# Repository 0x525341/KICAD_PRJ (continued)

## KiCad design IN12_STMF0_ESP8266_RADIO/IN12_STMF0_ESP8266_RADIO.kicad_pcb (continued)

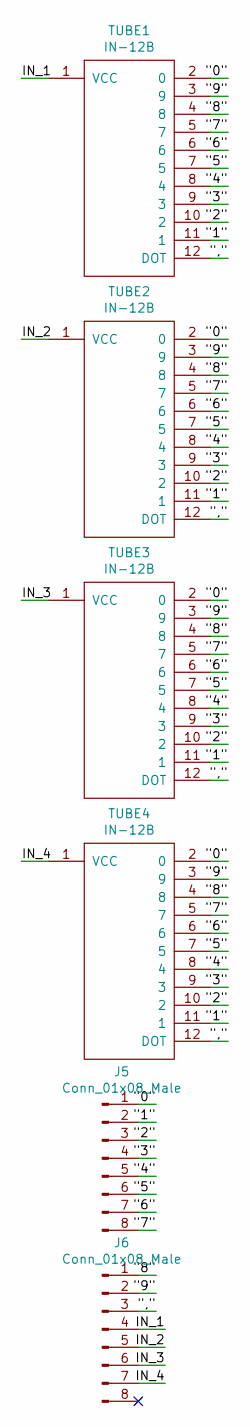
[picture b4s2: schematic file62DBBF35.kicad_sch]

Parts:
J5, J6: Conn_01x08_Male; PinHeader_1x08_P2.54mm_Vertical
TUBE1, TUBE2, TUBE3, TUBE4: IN-12B

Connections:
/Sheet62DBBF35/"0": J5.1, TUBE1.2 (0), TUBE2.2 (0), TUBE3.2 (0), TUBE4.2 (0)
/Sheet62DBBF35/"1": J5.2, TUBE1.11 (1), TUBE2.11 (1), TUBE3.11 (1), TUBE4.11 (1)
/Sheet62DBBF35/"2": J5.3, TUBE1.10 (2), TUBE2.10 (2), TUBE3.10 (2), TUBE4.10 (2)
/Sheet62DBBF35/"3": J5.4, TUBE1.9 (3), TUBE2.9 (3), TUBE3.9 (3), TUBE4.9 (3)
/Sheet62DBBF35/"4": J5.5, TUBE1.8 (4), TUBE2.8 (4), TUBE3.8 (4), TUBE4.8 (4)
/Sheet62DBBF35/"5": J5.6, TUBE1.7 (5), TUBE2.7 (5), TUBE3.7 (5), TUBE4.7 (5)
/Sheet62DBBF35/"6": J5.7, TUBE1.6, TUBE2.6, TUBE3.6, TUBE4.6
/Sheet62DBBF35/"7": J5.8, TUBE1.5 (7), TUBE2.5 (7), TUBE3.5 (7), TUBE4.5 (7)
/Sheet62DBBF35/"8": J6.1, TUBE1.4 (8), TUBE2.4 (8), TUBE3.4 (8), TUBE4.4 (8)
/Sheet62DBBF35/"9": J6.2, TUBE1.3 (9), TUBE2.3 (9), TUBE3.3 (9), TUBE4.3 (9)
/Sheet62DBBF35/",": J6.3, TUBE1.12 (DOT), TUBE2.12 (DOT), TUBE3.12 (DOT), TUBE4.12 (DOT)
/Sheet62DBBF35/IN_1: J6.4, TUBE1.1 (VCC)
/Sheet62DBBF35/IN_2: J6.5, TUBE2.1 (VCC)
/Sheet62DBBF35/IN_3: J6.6, TUBE3.1 (VCC)
/Sheet62DBBF35/IN_4: J6.7, TUBE4.1 (VCC)

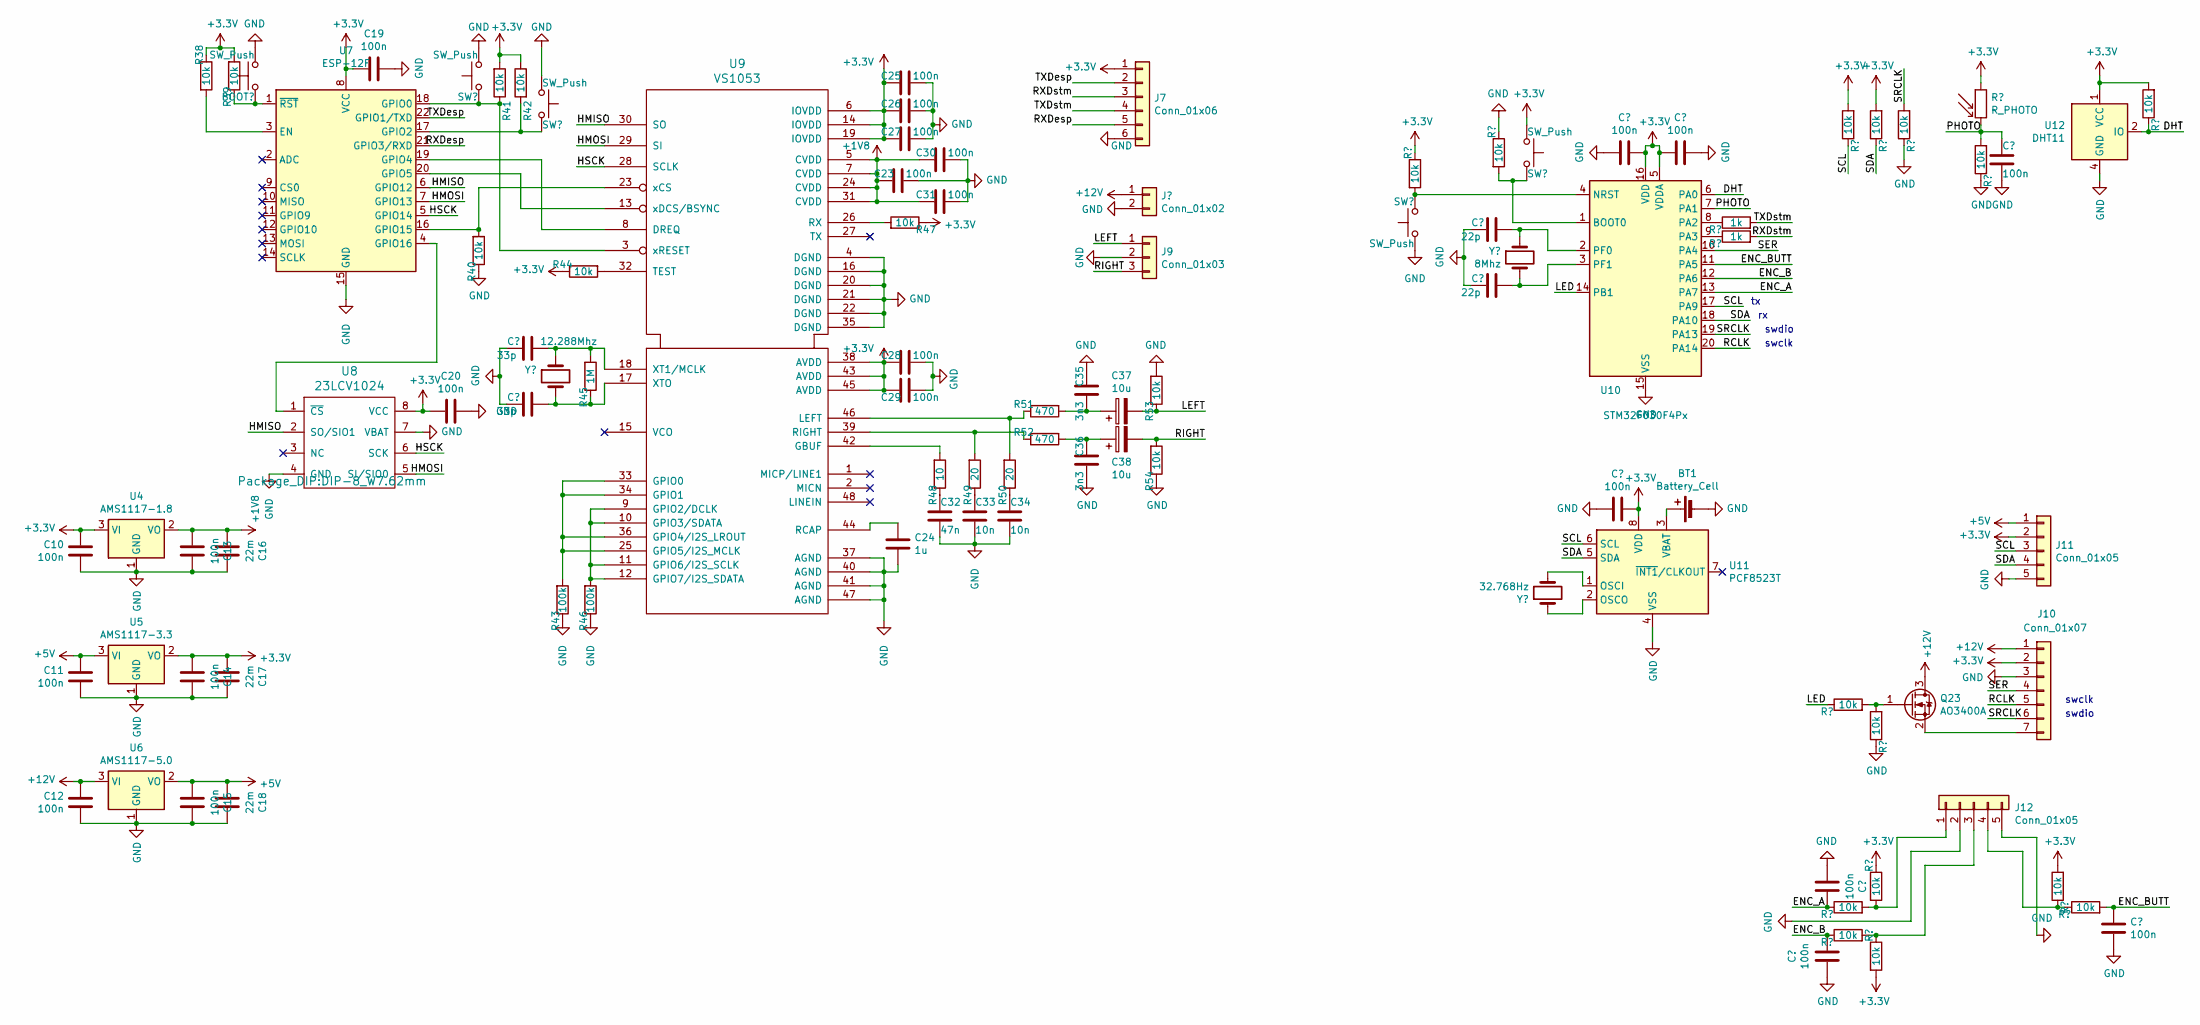
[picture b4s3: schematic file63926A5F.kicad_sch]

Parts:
BOOT1, BOOT2, BOOT3: SW_Push; SW_SPST_B3U-1000P
BT1: Battery_Cell; PinHeader_1x02_P2.54mm_Vertical
C10, C11, C12, C13, C14, C15, C19, C20, C23, C25, C26, C27, C28, C29, C30, C31, C41, C42, C43, C44, C45, C46, C47: 100n; C_1206_3216Metric
C16, C17, C18: 22m; C_1206_3216Metric
C21, C22: 33p; C_1206_3216Metric
C24: 1u; C_1206_3216Metric
C32: 47n; C_1206_3216Metric
C33, C34: 10n; C_1206_3216Metric
C35, C36: 3n3; C_1206_3216Metric
C37, C38: 10u; CP_Radial_D5.0mm_P2.00mm
C39, C40: 22p; C_1206_3216Metric
J7: Conn_01x06; PinHeader_1x06_P2.54mm_Vertical
J8: Conn_01x02; TerminalBlock_Phoenix_PT-1,5-2-5.0-H_1x02_P5.00mm_Horizontal
J9: Conn_01x03; PinHeader_1x03_P2.54mm_Vertical
J10: Conn_01x07; PinSocket_1x07_P2.54mm_Vertical
J11, J12: Conn_01x05; PinHeader_1x05_P2.54mm_Vertical
Q23: AO3400A; SOT-23
R38, R39, R40, R41, R42, R44, R47, R53, R54, R55, R56, R57, R58, R61, R62, R63, R64, R65, R66, R67, R69, R70, R71, R72: 10k; R_1206_3216Metric
R43, R46: 100k; R_1206_3216Metric
R45: 1M; R_1206_3216Metric
R48: 10; R_1206_3216Metric
R49, R50: 20; R_1206_3216Metric
R51, R52: 470; R_1206_3216Metric
R59, R60: 1k; R_1206_3216Metric
R68: R_PHOTO; R_LDR_4.9x4.2mm_P2.54mm_Vertical
RST1, RST2: SW_Push; SW_SPST_B3U-1000P
U4: AMS1117-1.8; SOT-223-3_TabPin2
U5: AMS1117-3.3; SOT-223-3_TabPin2
U6: AMS1117-5.0; SOT-223-3_TabPin2
U7: ESP-12F; ESP-12E
U8: 23LCV1024; DIP-8_W7.62mm
U9: VS1053; LQFP-48_7x7mm_P0.5mm
U10: STM32F030F4Px; TSSOP-20_4.4x6.5mm_P0.65mm
U11: PCF8523T; SOIC-8_3.9x4.9mm_P1.27mm
U12: DHT11; Aosong_DHT11_5.5x12.0_P2.54mm
Y1: 12.288Mhz; Crystal_HC49-4H_Vertical
Y2: 32.768Hz; Crystal_Round_D3.0mm_Vertical
Y3: 8Mhz; Crystal_HC49-4H_Vertical

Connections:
+1V8: C13.2, C16.2, C23.1, C30.1, C31.1, U4.2 (VO), U9.5 (CVDD), U9.7 (CVDD), U9.24 (CVDD), U9.31 (CVDD)
+3V3: BOOT3.2, C10.2, C14.2, C17.2, C19.2, C20.1, C25.1, C26.1, C27.1, C28.1, C29.1, C41.2, C42.2, C43.2, J7.1, J10.2, J11.2, R38.1, R39.2, R41.2, R42.1, R44.1, R47.1, R58.1, R61.2, R64.2, R65.1, R66.2, R68.1, R70.2, R72.2, U4.3 (VI), U5.2 (VO), U7.8 (VCC), U8.8 (VCC), U9.6 (IOVDD), U9.14 (IOVDD), U9.19 (IOVDD), U9.38 (AVDD), U9.43 (AVDD), U9.45 (AVDD), U10.5 (VDDA), U10.16 (VDD), U11.8 (VDD), U12.1 (VCC); also elsewhere on the board
+5V: C11.2, C15.2, C18.2, J11.1, U5.3 (VI), U6.2 (VO)
+12V: C12.2, J8.1, J10.1, Q23.3 (D), U6.3 (VI); also elsewhere on the board
/Sheet63926A5F/BOOT: BOOT3.1, R55.2, U10.1 (BOOT0)
/Sheet63926A5F/DHT: R72.1, U10.6 (PA0), U12.2 (IO)
/Sheet63926A5F/ENC_A: C44.2, R62.1, U10.13 (PA7)
/Sheet63926A5F/ENC_B: C45.2, R63.1, U10.12 (PA6)
/Sheet63926A5F/ENC_BUTT: C47.2, R71.2, U10.11 (PA5)
/Sheet63926A5F/HMISO: U7.6 (GPIO12), U8.2 (SO/SIO1), U9.30 (SO)
/Sheet63926A5F/HMOSI: U7.7 (GPIO13), U8.5 (SI/SIO0), U9.29 (SI)
/Sheet63926A5F/HSCK: U7.5 (GPIO14), U8.6 (SCK), U9.28 (SCLK)
/Sheet63926A5F/LED: R56.1, U10.14 (PB1)
/Sheet63926A5F/LEFT: C37.2, J9.1, R53.1
/Sheet63926A5F/PHOTO: C46.1, R68.2, R69.2, U10.7 (PA1)
/Sheet63926A5F/RCLK: J10.5, U10.20 (PA14)
/Sheet63926A5F/RIGHT: C38.2, J9.3, R54.2
/Sheet63926A5F/RXDesp: J7.5, U7.21 (GPIO3/RXD)
/Sheet63926A5F/RXDstm: J7.3, R60.2
/Sheet63926A5F/SCL: J11.3, R61.1, U10.17 (PA9), U11.6 (SCL)
/Sheet63926A5F/SDA: J11.4, R64.1, U10.18 (PA10), U11.5 (SDA)
/Sheet63926A5F/SER: J10.4, U10.10 (PA4)
/Sheet63926A5F/SRCLK: J10.6, R67.2, U10.19 (PA13)
/Sheet63926A5F/TXDesp: J7.2, U7.22 (GPIO1/TXD)
/Sheet63926A5F/TXDstm: J7.4, R59.2
unnamed: BOOT1.1, R41.1, U7.18 (GPIO0), U9.3 (xRESET)
unnamed: BOOT2.1, R42.2, U7.17 (GPIO2)
unnamed: BT1.1 (+), U11.3 (VBAT)
unnamed: C21.1, R45.2, U9.18 (XT1/MCLK), Y1.1
unnamed: C22.1, R45.1, U9.17 (XTO), Y1.2
unnamed: C24.2, U9.44 (RCAP)
unnamed: C32.1, R48.1
unnamed: C33.1, R49.1
unnamed: C34.1, R50.1
unnamed: C35.2, C37.1, R51.2
unnamed: C36.1, C38.1, R52.2
unnamed: C39.1, U10.2 (PF0), Y3.1
unnamed: C40.1, U10.3 (PF1), Y3.2
unnamed: J10.7, Q23.2 (S)
unnamed: J12.1, R62.2, R65.2
unnamed: J12.3, R63.2, R66.1
unnamed: J12.4, R70.1, R71.1
unnamed: Q23.1 (G), R56.2, R57.2
unnamed: R38.2, U7.3 (EN)
unnamed: R39.1, RST2.1, U7.1 (~RST)
unnamed: R40.2, U7.16 (GPIO15), U9.23 (xCS)
unnamed: R43.2, U9.25 (GPIO5/I2S_MCLK), U9.33 (GPIO0), U9.34 (GPIO1), U9.36 (GPIO4/I2S_LROUT)
unnamed: R44.2, U9.32 (TEST)
unnamed: R46.2, U9.9 (GPIO2/DCLK), U9.10 (GPIO3/SDATA), U9.11 (GPIO6/I2S_SCLK), U9.12 (GPIO7/I2S_SDATA)
unnamed: R47.2, U9.26 (RX)
unnamed: R48.2, U9.42 (GBUF)
unnamed: R49.2, R52.1, U9.39 (RIGHT)
unnamed: R50.2, R51.1, U9.46 (LEFT)
unnamed: R58.2, RST1.1, U10.4 (NRST)
unnamed: R59.1, U10.8 (PA2)
unnamed: R60.1, U10.9 (PA3)
unnamed: U7.4 (GPIO16), U8.1 (~CS)
unnamed: U7.19 (GPIO4), U9.8 (DREQ)
unnamed: U7.20 (GPIO5), U9.13 (xDCS/BSYNC)
unnamed: U11.1 (OSCI), Y2.2
unnamed: U11.2 (OSCO), Y2.1

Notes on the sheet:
swdio
swclk

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
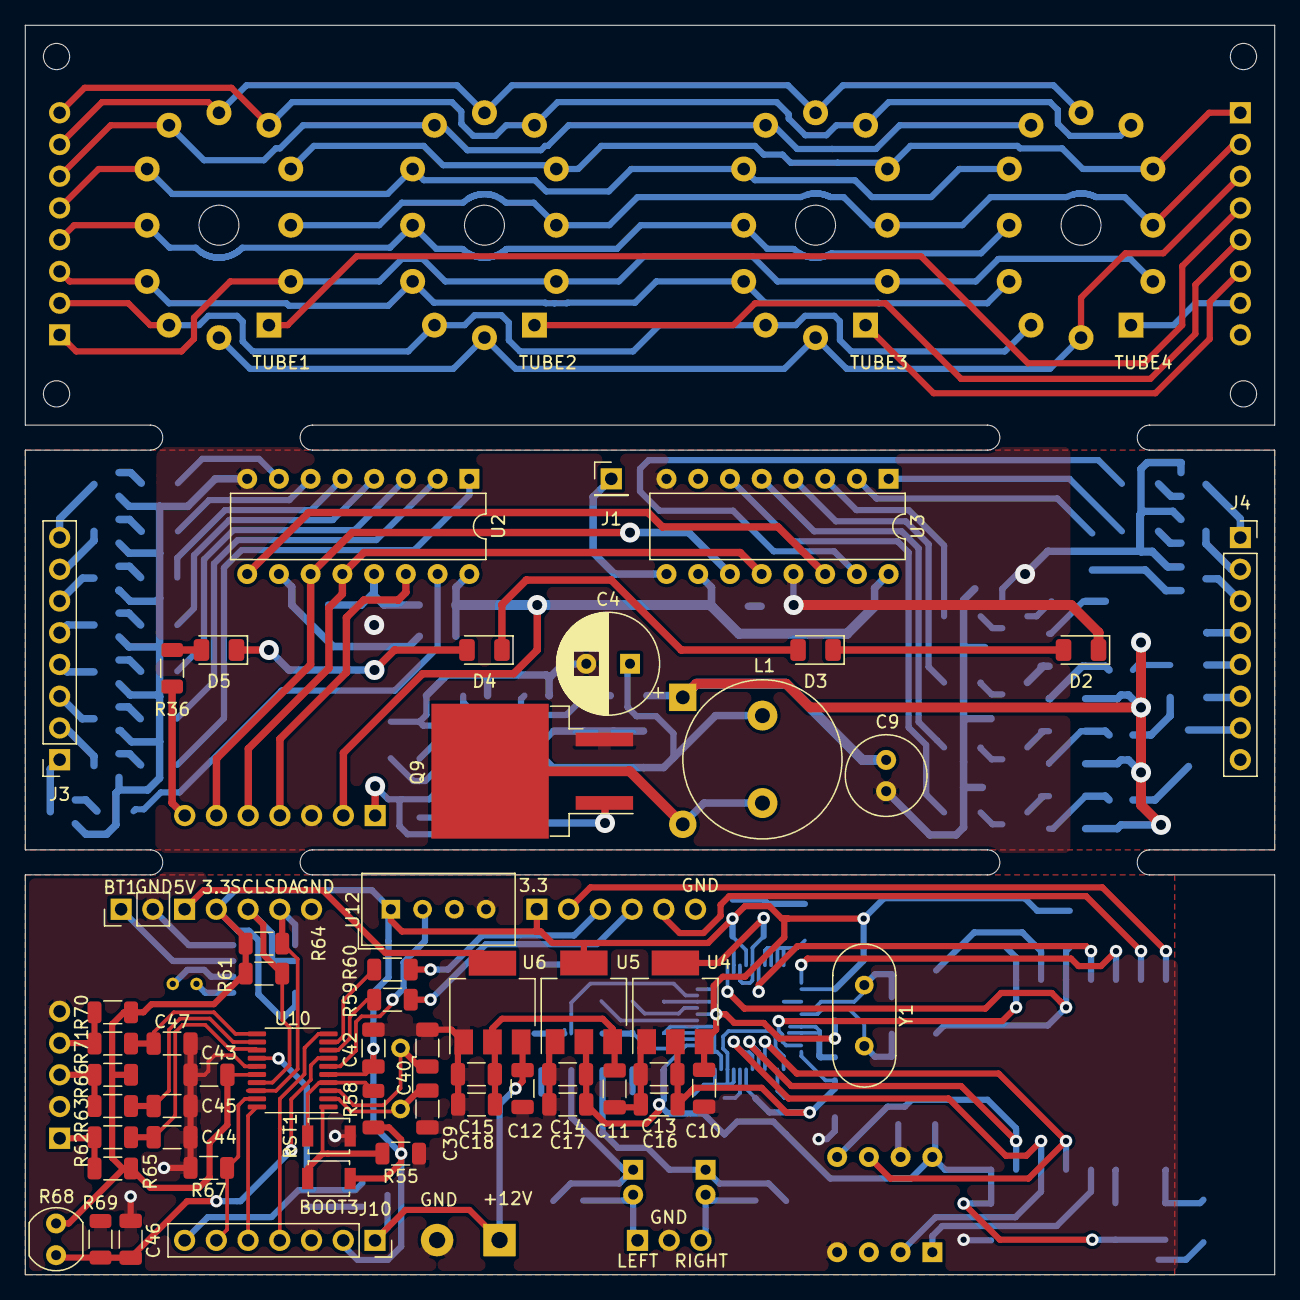
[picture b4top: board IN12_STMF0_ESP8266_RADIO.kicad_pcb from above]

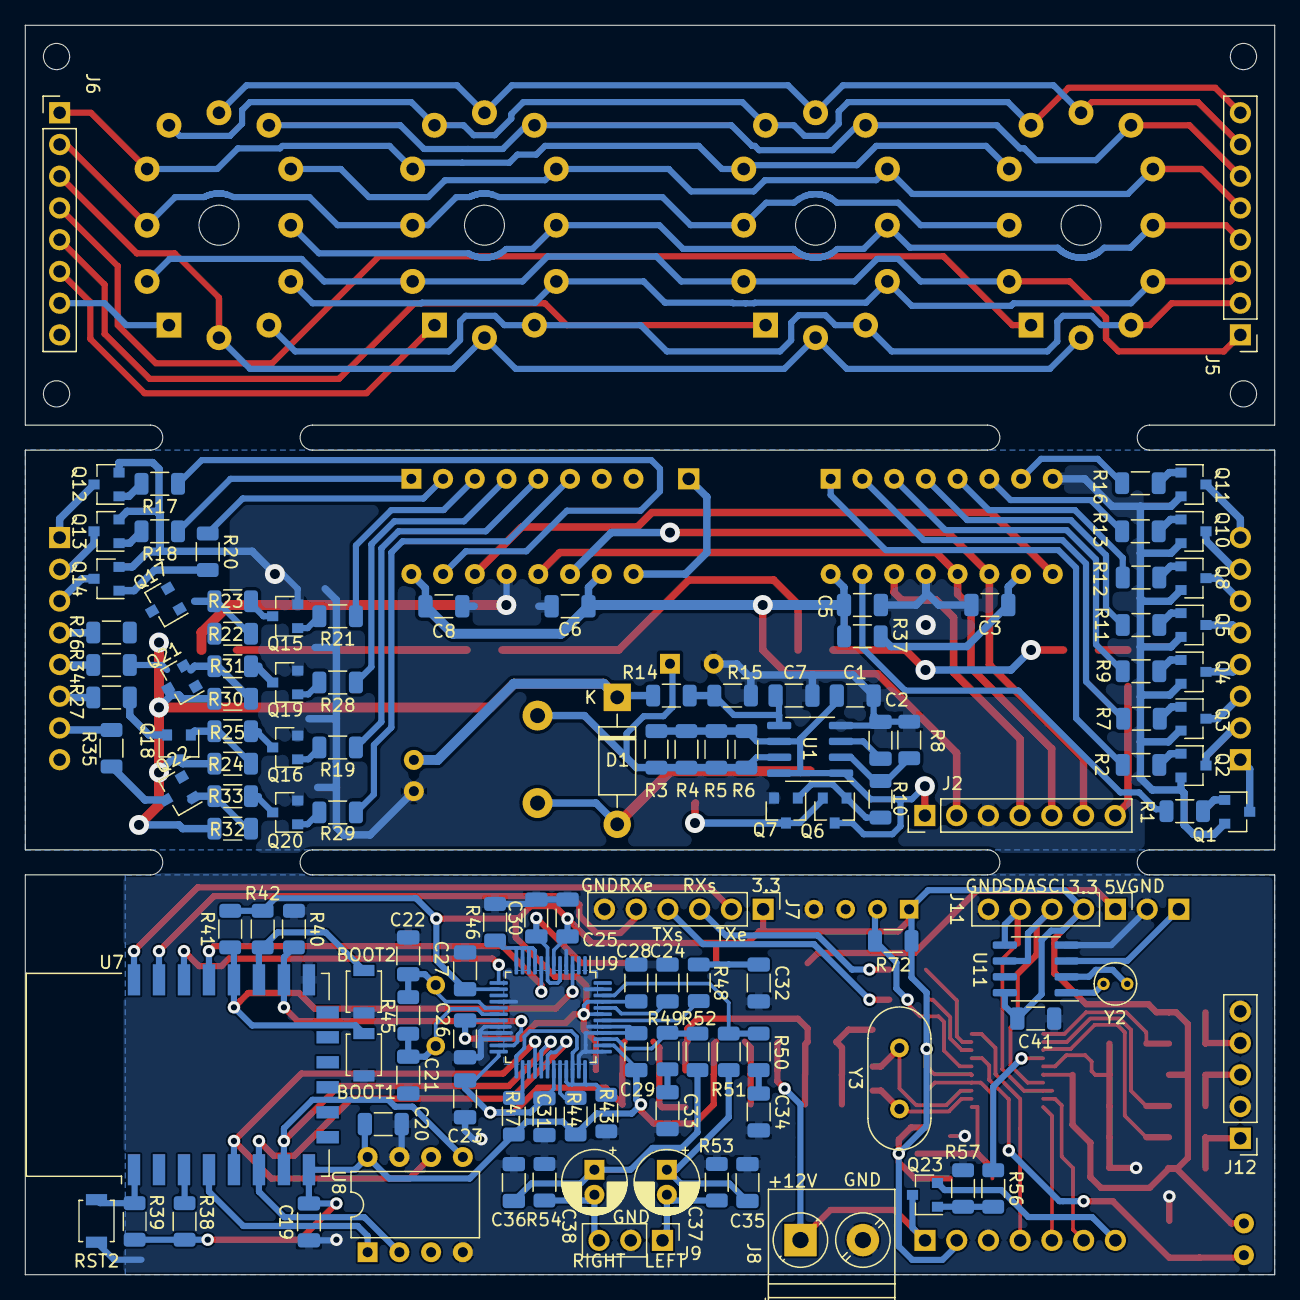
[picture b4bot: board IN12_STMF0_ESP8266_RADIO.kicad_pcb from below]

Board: 2 copper layers, 100.0 x 100.0 mm, 185 parts (125 on the bottom side), 152 nets.

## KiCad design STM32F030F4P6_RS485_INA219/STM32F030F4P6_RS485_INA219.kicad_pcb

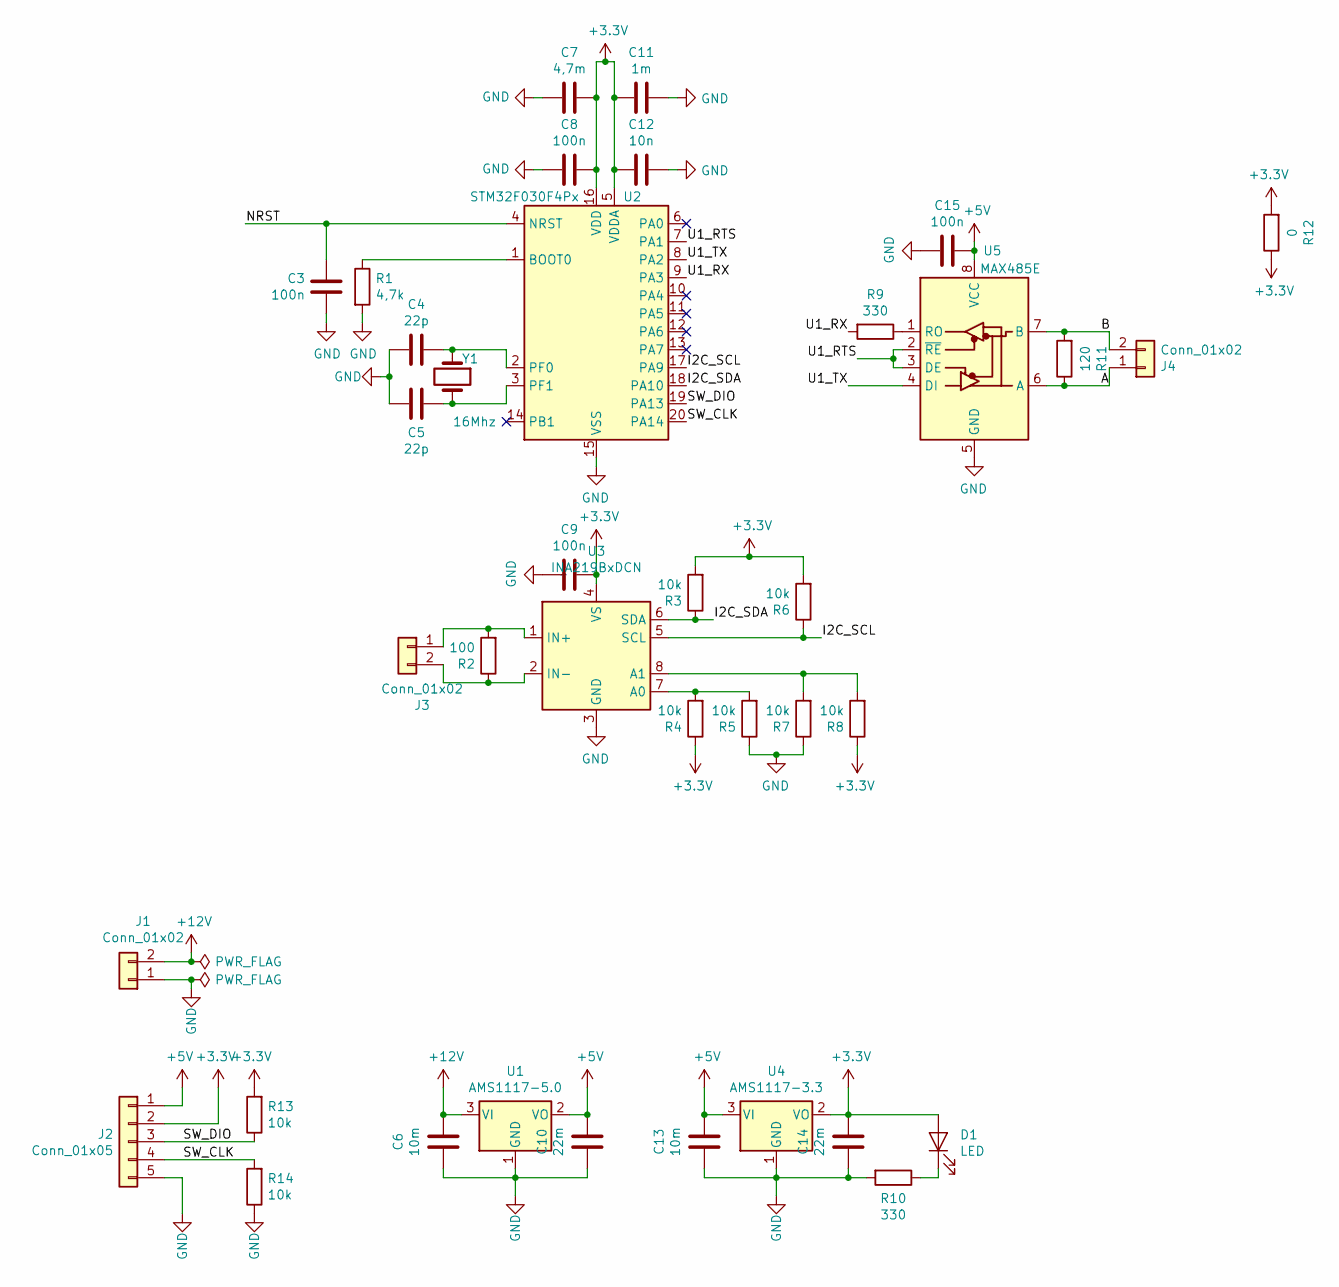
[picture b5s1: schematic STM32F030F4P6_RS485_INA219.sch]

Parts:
C3, C8, C9, C15: 100n; C_1206_3216Metric_Pad1.42x1.75mm_HandSolder
C4, C5: 22p; C_1206_3216Metric_Pad1.42x1.75mm_HandSolder
C6, C13: 10m; C_1206_3216Metric_Pad1.42x1.75mm_HandSolder
C7: 4,7m; C_1206_3216Metric_Pad1.42x1.75mm_HandSolder
C10, C14: 22m; C_1206_3216Metric_Pad1.42x1.75mm_HandSolder
C11: 1m; C_1206_3216Metric_Pad1.42x1.75mm_HandSolder
C12: 10n; C_1206_3216Metric_Pad1.42x1.75mm_HandSolder
D1: LED; LED_1206_3216Metric_Pad1.42x1.75mm_HandSolder
J1, J3, J4: Conn_01x02; JST_NV_B02P-NV_1x02_P5.00mm_Vertical
J2: Conn_01x05; PinHeader_1x05_P2.54mm_Vertical
R1: 4,7k; R_1206_3216Metric_Pad1.42x1.75mm_HandSolder
R2: 100; R_4020_10251Metric_Pad1.65x5.30mm_HandSolder
R3, R4, R5, R6, R7, R8, R13, R14: 10k; R_1206_3216Metric_Pad1.42x1.75mm_HandSolder
R9, R10: 330; R_1206_3216Metric_Pad1.42x1.75mm_HandSolder
R11: 120; R_1206_3216Metric_Pad1.42x1.75mm_HandSolder
R12: 0; R_1206_3216Metric_Pad1.42x1.75mm_HandSolder
U1: AMS1117-5.0; SOT-223-3_TabPin2
U2: STM32F030F4Px; TSSOP-20_4.4x6.5mm_P0.65mm
U3: INA219BxDCN; SOT-23-8
U4: AMS1117-3.3; SOT-223-3_TabPin2
U5: MAX485E; SOIC-8_3.9x4.9mm_P1.27mm
Y1: 16Mhz; Crystal_HC49-4H_Vertical

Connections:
+3V3: C7.1, C8.1, C9.1, C11.2, C12.2, C14.2, D1.2 (A), J2.2, R3.2, R4.1, R6.2, R8.1, R12.1, R12.2, R13.2, U2.5 (VDDA), U2.16 (VDD), U3.4 (VS), U4.2 (VO)
+5V: C10.2, C13.2, C15.1, J2.1, U1.2 (VO), U4.3 (VI), U5.8 (VCC)
+12V: C6.2, J1.2, U1.3 (VI)
/A: J4.1, R11.1, U5.6 (A)
/B: J4.2, R11.2, U5.7 (B)
/I2C_SCL: R6.1, U2.17 (PA9), U3.5 (SCL)
/I2C_SDA: R3.1, U2.18 (PA10), U3.6 (SDA)
/NRST: C3.1, U2.4 (NRST)
/SW_CLK: J2.4, R14.2, U2.20 (PA14)
/SW_DIO: J2.3, R13.1, U2.19 (PA13)
/U1_RTS: U2.7 (PA1), U5.2 (~RE), U5.3 (DE)
/U1_RX: R9.2, U2.9 (PA3)
/U1_TX: U2.8 (PA2), U5.4 (DI)
GND: C3.2, C4.2, C5.2, C6.1, C7.2, C8.2, C9.2, C10.1, C11.1, C12.1, C13.1, C14.1, C15.2, J1.1, J2.5, R1.2, R5.1, R7.1, R10.2, R14.1, U1.1 (GND), U2.15 (VSS), U3.3 (GND), U4.1 (GND), U5.5 (GND)
unnamed: C4.1, U2.2 (PF0), Y1.1
unnamed: C5.1, U2.3 (PF1), Y1.2
unnamed: D1.1 (K), R10.1
unnamed: J3.1, R2.2, U3.1 (IN+)
unnamed: J3.2, R2.1, U3.2 (IN-)
unnamed: R1.1, U2.1 (BOOT0)
unnamed: R4.2, R5.2, U3.7 (A0)
unnamed: R7.2, R8.2, U3.8 (A1)
unnamed: R9.1, U5.1 (RO)

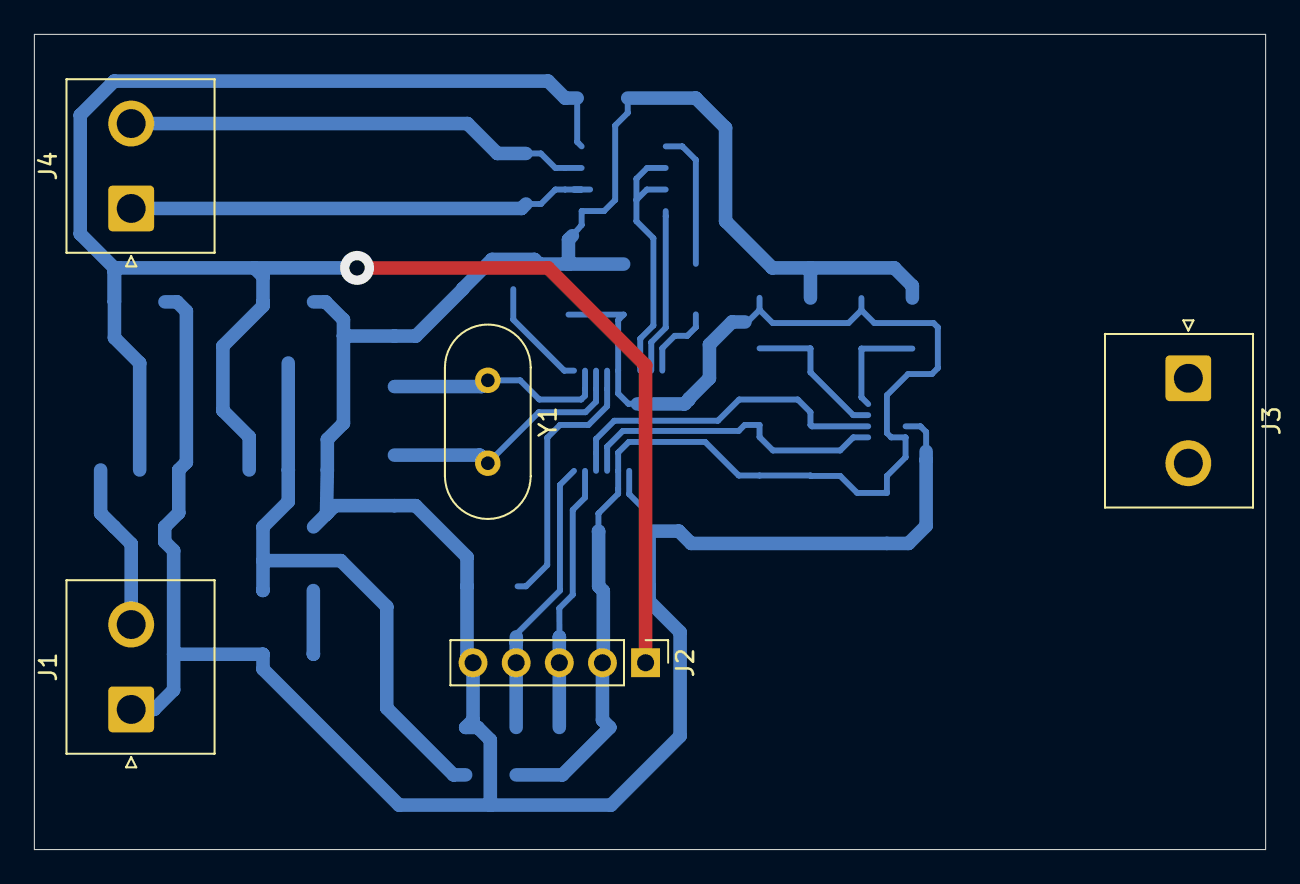
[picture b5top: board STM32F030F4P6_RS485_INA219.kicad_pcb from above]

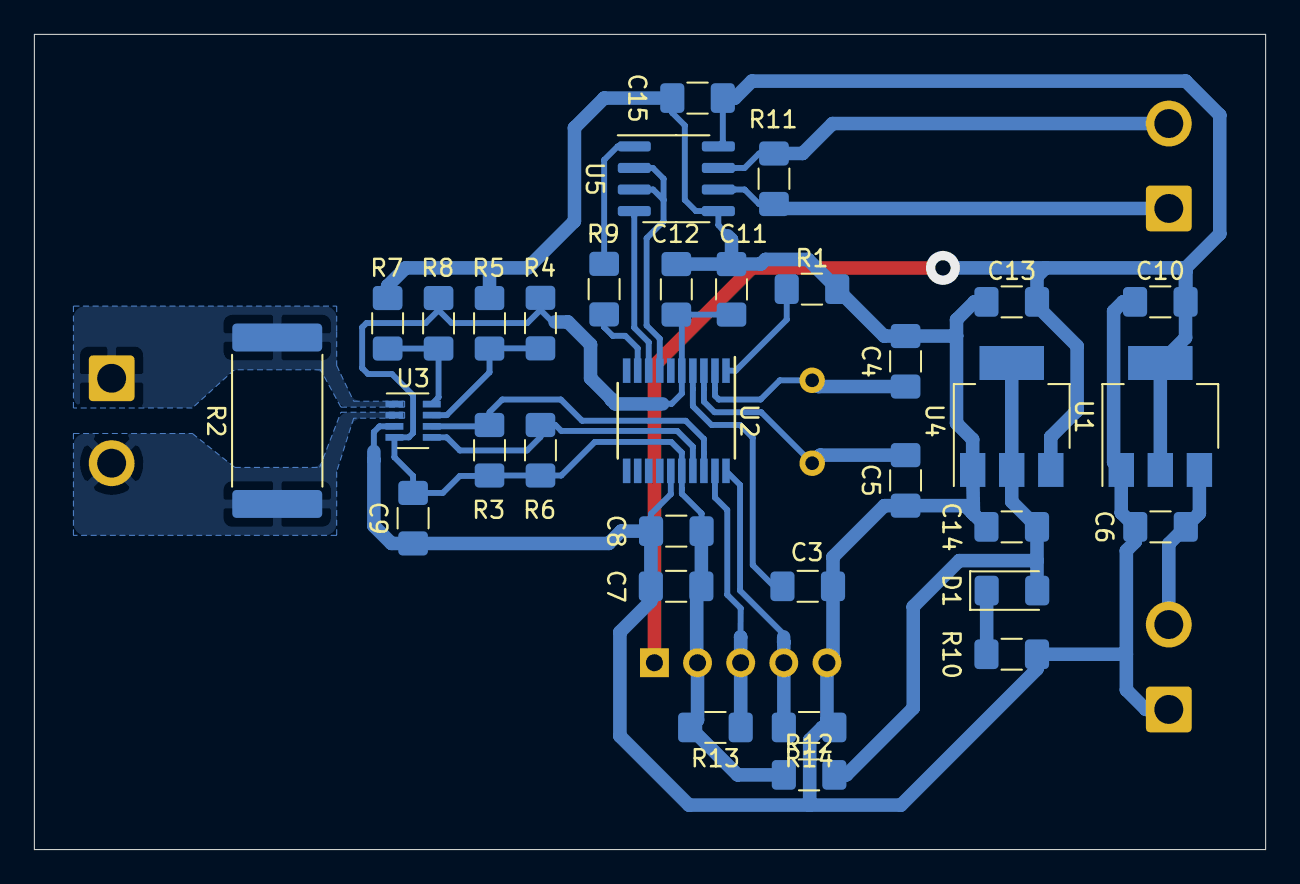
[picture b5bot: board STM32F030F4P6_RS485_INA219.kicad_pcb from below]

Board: 2 copper layers, 72.5 x 48.0 mm, 38 parts (33 on the bottom side), 23 nets.

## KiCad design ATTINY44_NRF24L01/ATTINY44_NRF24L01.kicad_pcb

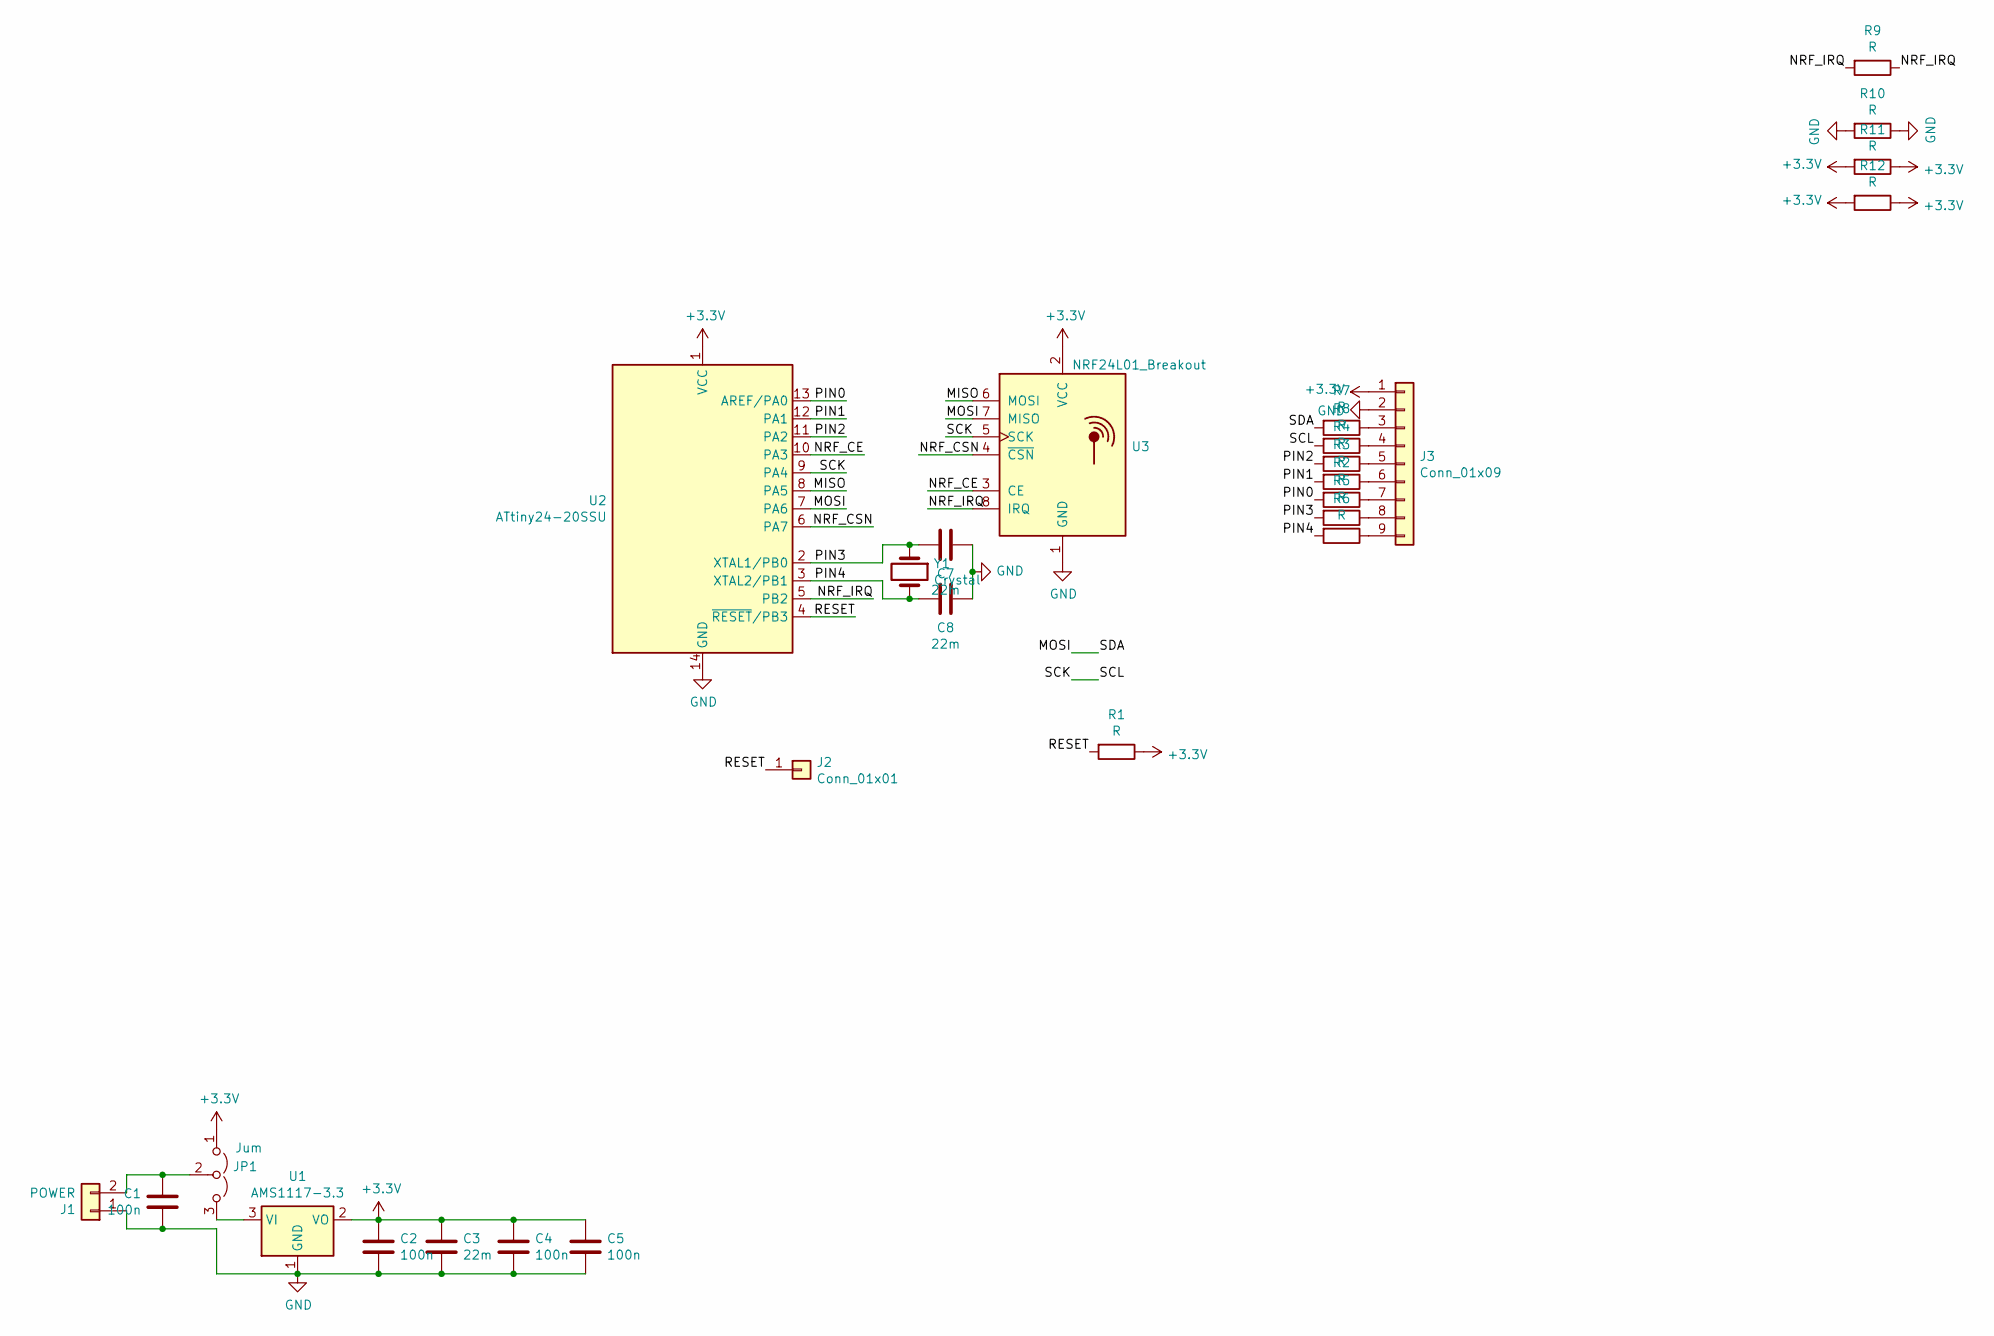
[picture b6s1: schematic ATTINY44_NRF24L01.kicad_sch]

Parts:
C1, C2, C4, C5: 100n; C_1206_3216Metric_Pad1.33x1.80mm_HandSolder
C3, C7, C8: 22m; C_1206_3216Metric_Pad1.33x1.80mm_HandSolder
J1: POWER; TerminalBlock_Phoenix_PT-1,5-2-5.0-H_1x02_P5.00mm_Horizontal
J2: Conn_01x01; PinHeader_1x01_P2.54mm_Vertical
J3: Conn_01x09; PinHeader_1x09_P2.54mm_Vertical
JP1: Jum; SolderJumper-3_P1.3mm_Open_Pad1.0x1.5mm
R1, R2, R3, R4, R5, R6, R7, R8, R9, R10, R11, R12: R; R_1206_3216Metric_Pad1.30x1.75mm_HandSolder
U1: AMS1117-3.3; SOT-223-3_TabPin2
U2: ATtiny24-20SSU; SOIC-14_3.9x8.7mm_P1.27mm
U3: NRF24L01_Breakout; nRF24L01_Breakout
Y1: Crystal; Crystal_HC49-4H_Vertical

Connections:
+3V3: C2.1, C3.1, C4.1, C5.1, J3.1, JP1.1 (A), R1.1, R11.1, R11.2, R12.1, R12.2, U1.2 (VO), U2.1 (VCC), U3.2 (VCC)
/MISO: U2.8 (PA5), U3.6 (MOSI)
/MOSI: R7.2, U2.7 (PA6), U3.7 (MISO)
/NRF_CE: U2.10 (PA3), U3.3 (CE)
/NRF_CSN: U2.6 (PA7), U3.4 (~CSN)
/NRF_IRQ: R9.1, R9.2, U2.5 (PB2), U3.8 (IRQ)
/PIN0: R2.2, U2.13 (AREF/PA0)
/PIN1: R3.2, U2.12 (PA1)
/PIN2: R4.2, U2.11 (PA2)
/PIN3: C7.2, R5.2, U2.2 (XTAL1/PB0), Y1.1
/PIN4: C8.2, R6.2, U2.3 (XTAL2/PB1), Y1.2
/RESET: J2.1, R1.2, U2.4 (~RESET/PB3)
/SCK: R8.2, U2.9 (PA4), U3.5 (SCK)
GND: C1.2, C2.2, C3.2, C4.2, C5.2, C7.1, C8.1, J1.1, J3.2, R10.1, R10.2, U1.1 (GND), U2.14 (GND), U3.1 (GND)
unnamed: C1.1, J1.2, JP1.2 (C)
unnamed: J3.3, R7.1
unnamed: J3.4, R8.1
unnamed: J3.5, R4.1
unnamed: J3.6, R3.1
unnamed: J3.7, R2.1
unnamed: J3.8, R5.1
unnamed: J3.9, R6.1
unnamed: JP1.3 (B), U1.3 (VI)

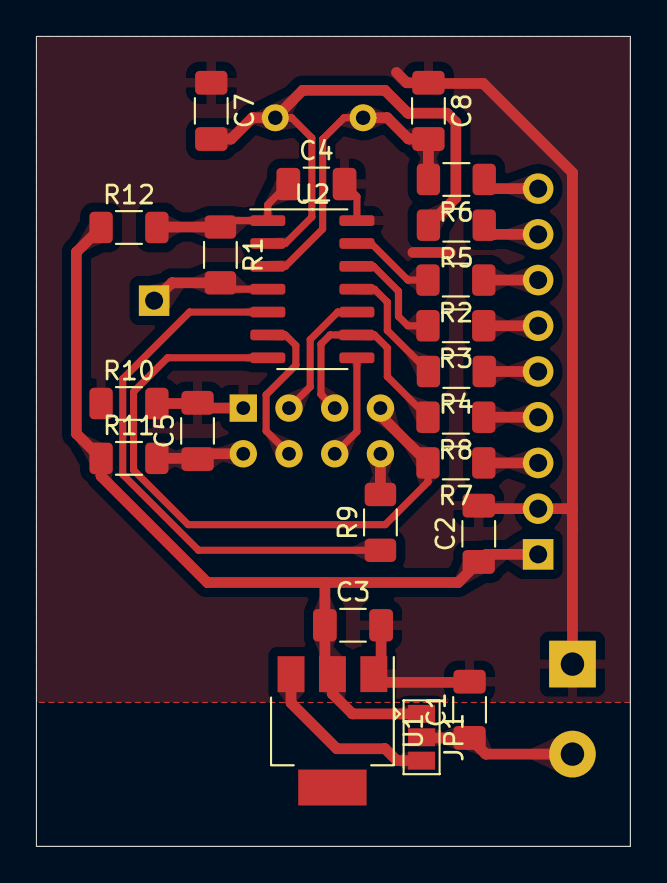
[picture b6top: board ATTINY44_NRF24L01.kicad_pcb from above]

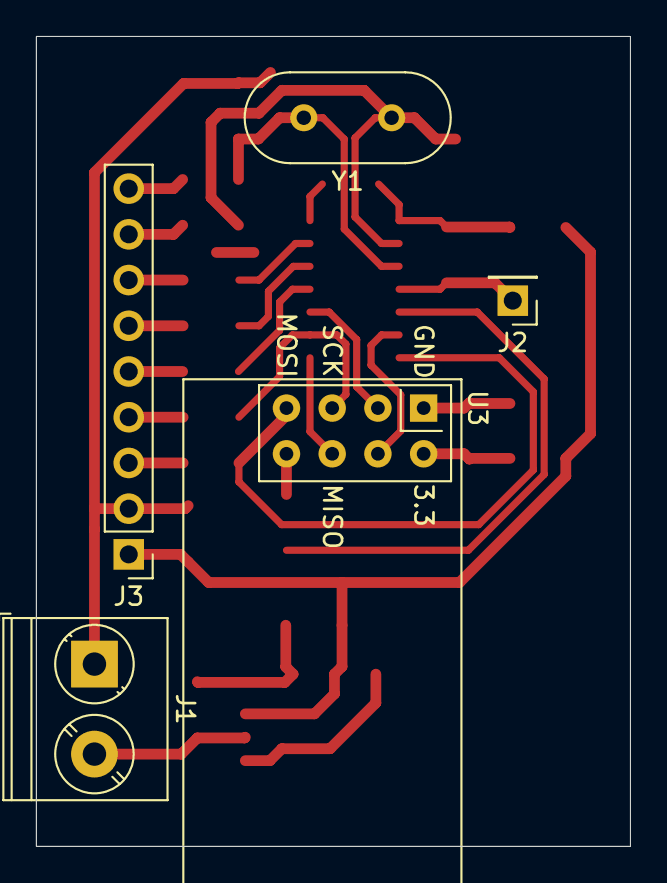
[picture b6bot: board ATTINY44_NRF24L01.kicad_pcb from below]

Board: 2 copper layers, 33.0 x 45.0 mm, 27 parts (5 on the bottom side), 23 nets.
